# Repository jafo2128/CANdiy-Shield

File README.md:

# CANdiy-Shield
The CANdiy-Shield is a plug-on module for Arduino/Genuino with CAN-Bus (Controller Area Network) connectivity.

## Shop
* [CANdiy-Shield](http://www.watterott.com/en/Arduino-CANdiy-Shield)
* [Railuino Components](http://www.watterott.com/en/Railuino-components)
* [OBD2-Connector](http://www.watterott.com/en/OBD2-Connector-With-PCB)

## Features
* Microchip MCP2515 CAN Controller (SPI)
* Microchip MCP2562 CAN Transceiver (CANdiy-Shield v1.x: MCP2551)
* Switchable between 3V3 or 5V logic level
* 2 CAN connectors (RJ45)
* Prototyping Area
* Compatible with all Arduino/Genuino Boards (SPI connection via 6-Pin ISP connector)

## Hardware and Software
* [Schematics + Layout](https://github.com/watterott/CANdiy-Shield/tree/master/hardware)
* [Arduino Library and Examples](https://github.com/watterott/Arduino-Libs)

## Projects
* Railuino (Maerklin Model Railways): http://code.google.com/p/railuino/
  [German Documentation](https://railuino.googlecode.com/files/2013-08-01-Railuino-Directors-Cut.pdf),
  [German Forum](http://www.stummiforum.de/viewtopic.php?t=90072),
  [German Magazine Article](https://shop.heise.de/katalog/ct-hardware-hacks-1-2013),
  [English Documentation](http://www.yaasan.mints.ne.jp/railuino.html),
  [French Documentation](http://mchobby.be/wiki/index.php?title=Railuino)
* Mechanic (OBD-II Interface): http://code.google.com/p/mechanic/
* Electricity on Tap: http://www.terabatt.com/makerscorner.html
* WikiCAN (OBD On-Board-Diagnostics): http://www.wikican.uni-bayreuth.de/wikican/index.php?title=WikiCAN-Arduino
* MERG CBUS (Model Railways): http://www.oscale.net/cbus http://www.merg.org.uk/merg_resources/cbus.php

Finally words from us Archivers and Developers.. 

##### Donate

People from time to time wish to donate a little money. Donating won't get you anything special, other than a warm feeling inside, and possibly urge me to produce more freely available material for interesting projects. You can donate via [PayPal](https://www.paypal.com), just click [donate](https://www.paypal.com/cgi-bin/webscr?cmd=_s-xclick&hosted_button_id=3PXVSLXFBS45E) button available below - it will redirect you to the secured PayPal page where you can provide donation amount (there is no minimal value). Any donations are apreciated greatly, and we thank you all in advance for your support along the ways..

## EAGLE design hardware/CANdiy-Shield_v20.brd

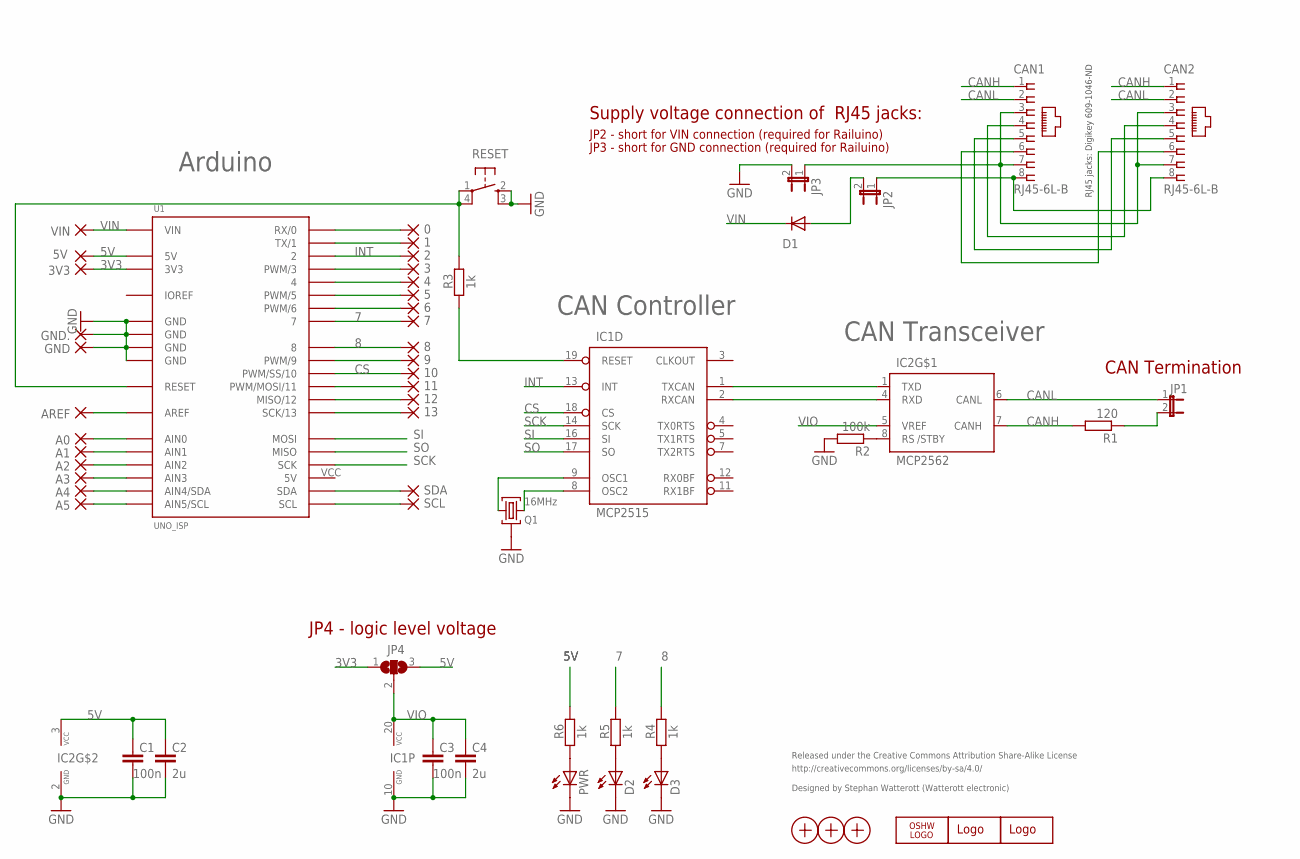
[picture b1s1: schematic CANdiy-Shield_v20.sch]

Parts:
0, 1, 2, 3, 3V3, 4, 5, 5V, 6, 7, 8, 9, 10, 11, 12, 13: 1,6/0,8
A0, A1, A2, A3, A4, A5: 1,6/0,8
AREF: 1,6/0,8
C1, C3: 100n; C0603
C2, C4: 2u; C0603
CAN1, CAN2: RJ45-6L-B; RJ45-NO-SHIELD
D1: CGRM4001-G; SOD-123_MINI-SMA
D2, D3: LEDCHIPLED_0603; CHIPLED_0603
GND, GND.: 1,6/0,8
IC1: MCP2515; TSSOP20
IC2: MCP2562; SO08
JP1, JP2, JP3: JP1E; JP1
JP4: SJ2W; SJ_2
LOGO1: LOGO-SPARK_PLACE; SPARK_TPLACE
LOGO2: OSHW_LOGO_6MILX0100-NT; OSHW_6X100_NOTEXT
PWR: LEDCHIPLED_0603; CHIPLED_0603
Q1: 16MHz; SMD_OSC_35X15
R1: 120; R0603
R2: 100k; R0603
R3, R4, R5, R6: 1k; R0603
RESET: SW_SMDS; SW_SMD4
SCL: 1,6/0,8
SDA: 1,6/0,8
U1: UNO_ISP
U$1: WE-LOGO
VIN: 1,6/0,8
X1, X2, X3: PASSER

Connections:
0: 0.1, U1.0 (RX/0)
1: 1.1, U1.1 (TX/1)
3: 3.1, U1.3 (PWM/3)
3V3: 3V3.1, JP4.1, U1.3V3
4: 4.1, U1.4
5: 5.1, U1.5 (PWM/5)
5V: 5V.1, C1.1, C2.1, IC2.3 (VCC), JP4.3, R6.1, U1.5V
6: 6.1, U1.6 (PWM/6)
7: 7.1, R5.1, U1.7
8: 8.1, R4.1, U1.8
9: 9.1, U1.9 (PWM/9)
11: 11.1, U1.11 (PWM/MOSI/11)
12: 12.1, U1.12 (MISO/12)
13: 13.1, U1.13 (SCK/13)
A0: A0.1, U1.AIN0
A1: A1.1, U1.AIN1
A2: A2.1, U1.AIN2
A3: A3.1, U1.AIN3
A4: A4.1, U1.AIN4 (AIN4/SDA)
A5: A5.1, U1.AIN5 (AIN5/SCL)
AREF: AREF.1, U1.AREF
CANH: CAN1.1, CAN2.1, IC2.7 (CANH), R1.2
CANL: CAN1.2, CAN2.2, IC2.6 (CANL), JP1.1
CAN_RX: IC1.2 (RXCAN), IC2.4 (RXD)
CAN_TX: IC1.1 (TXCAN), IC2.1 (TXD)
CS: 10.1, IC1.18 (CS), U1.10 (PWM/SS/10)
GND: C1.2, C2.2, C3.2, C4.2, D2.C, D3.C, GND.1, GND..1, IC1.10 (GND), IC2.2 (GND), JP3.2, PWR.C, Q1.GND, R2.2, RESET.2 (S), RESET.3 (S1), U1.GND@1 (GND), U1.GND@2 (GND), U1.GND@3 (GND), U1.GND@4 (GND)
INT: 2.1, IC1.13 (INT), U1.2
IOREF: U1.IOREF
unnamed: IC1.19 (RESET), R3.2
unnamed: CAN1.8, CAN2.8, JP2.1
unnamed: IC2.8 (RS), R2.1
unnamed: CAN1.3, CAN1.7, CAN2.3, CAN2.7, JP3.1
unnamed: JP1.2, R1.1
unnamed: SCL.1, U1.SCL
unnamed: SDA.1, U1.SDA
unnamed: D3.A, R4.2
unnamed: PWR.A, R6.2
unnamed: D2.A, R5.2
unnamed: D1.A, JP2.2
unnamed: CAN1.4, CAN2.4
unnamed: CAN1.5, CAN2.5
unnamed: CAN1.6, CAN2.6
OSC1: IC1.9 (OSC1), Q1.1
OSC2: IC1.8 (OSC2), Q1.2
RESET: R3.1, RESET.1, RESET.4 (P1), U1.RST (RESET)
SCK: IC1.14 (SCK), U1.SCK
SI: IC1.16 (SI), U1.MOSI
SO: IC1.17 (SO), U1.MISO
VIN: D1.C, U1.VIN, VIN.1
VIO: C3.1, C4.1, IC1.20 (VCC), IC2.5 (VREF), JP4.2

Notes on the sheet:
Released under the Creative Commons Attribution Share-Alike License
http://creativecommons.org/licenses/by-sa/4.0/
Designed by Stephan Watterott (Watterott electronic)
Arduino
CAN Termination
Supply voltage connection of RJ45 jacks:
JP3 - short for GND connection (required for Railuino)
JP2 - short for VIN connection (required for Railuino)
RJ45 jacks: Digikey 609-1046-ND
CAN Controller
CAN Transceiver
JP4 - logic level voltage
/STBY

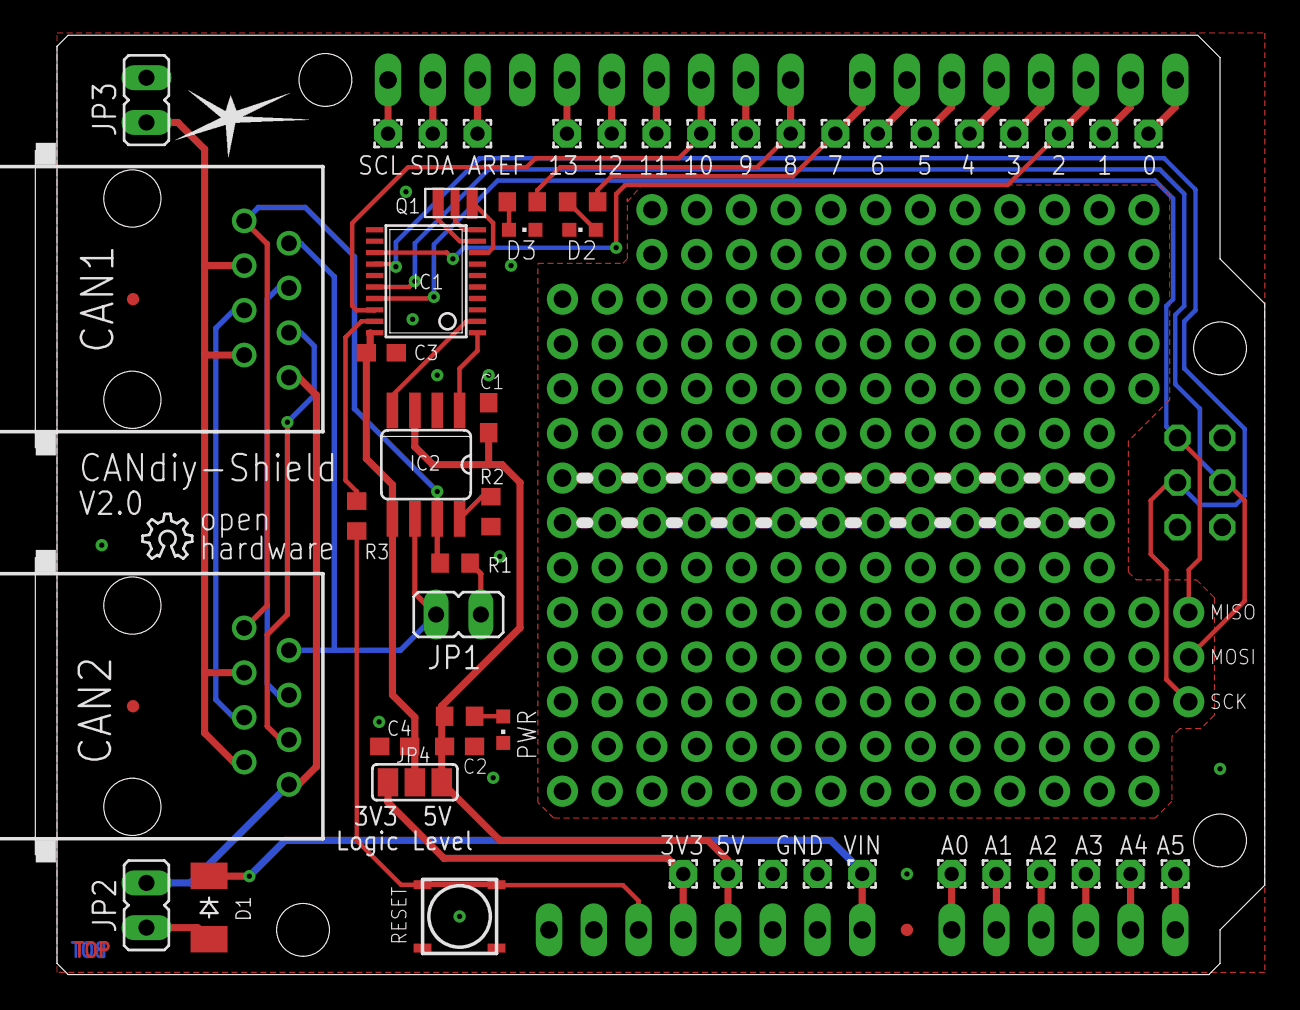
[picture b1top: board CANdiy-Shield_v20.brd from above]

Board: 2 copper layers, 69.8 x 53.3 mm, 59 parts (1 on the bottom side), 50 nets.

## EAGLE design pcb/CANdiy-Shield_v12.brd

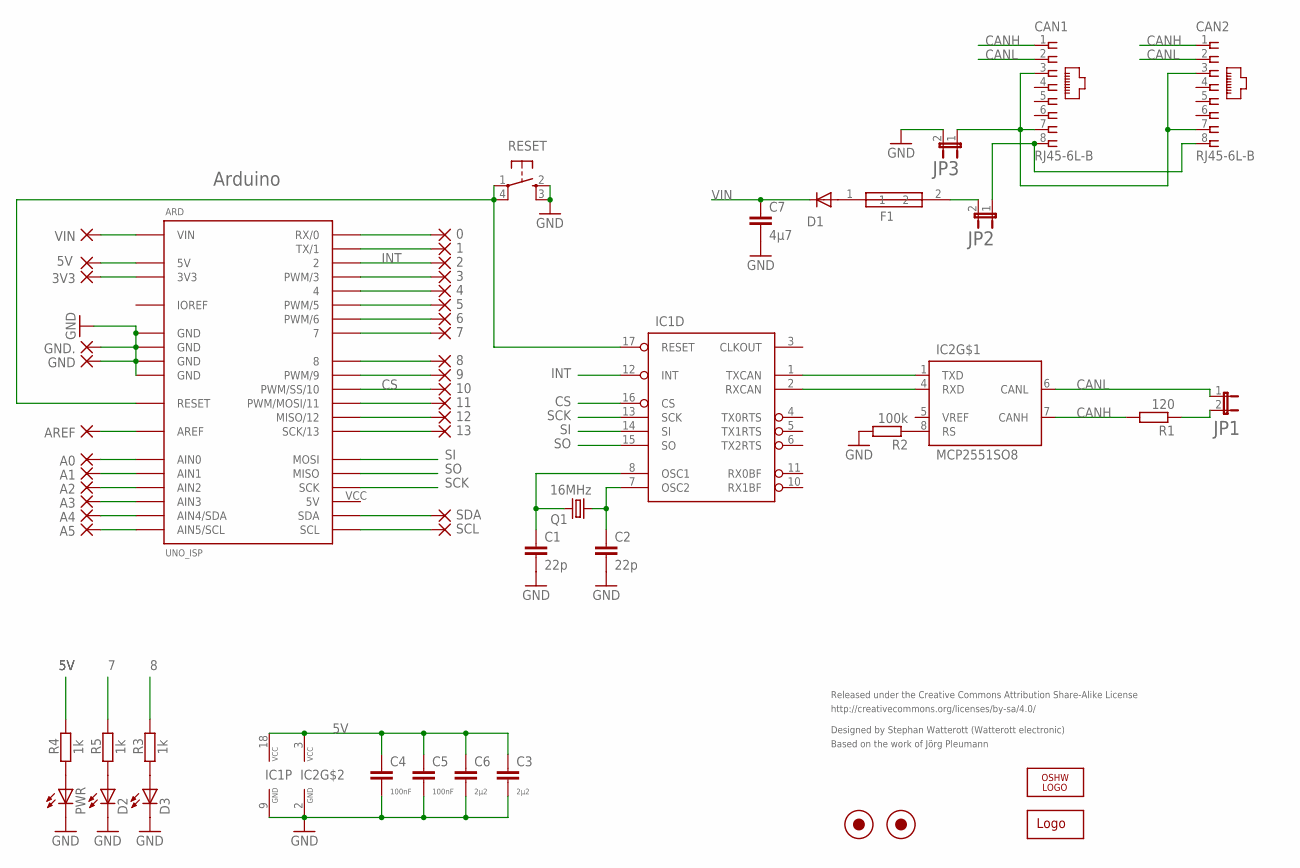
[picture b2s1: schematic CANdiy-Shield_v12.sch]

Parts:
0, 1, 2, 3, 3V3, 4, 5, 5V, 6, 7, 8, 9, 10, 11, 12, 13: 1,6/0,8
A0, A1, A2, A3, A4, A5: 1,6/0,8
ARD: UNO_ISP
AREF: 1,6/0,8
C1, C2: 22p; C0603
C3, C6: 2µ2; C0603
C4, C5: 100nF; C0603
C7: 4µ7; C1206
CAN1, CAN2: RJ45-6L-B; RJ45-NO-SHIELD
D1: CGRM4001-G; SOD-123_MINI-SMA
D2, D3: LEDCHIPLED_0603; CHIPLED_0603
F1: F1; L1812
GND, GND.: 1,6/0,8
IC1: MCP2515SO; SO-18W
IC2: MCP2551SO8; SO08
JP1, JP2, JP3: JP1E; JP1
LOGO2: OSHW_LOGO_6MILX0100-NT; OSHW_6X100_NOTEXT
PWR: LEDCHIPLED_0603; CHIPLED_0603
Q1: 16MHz; HC49UP
R1: 120; R0603
R2: 100k; R0603
R3, R4, R5: 1k; R0603
RESET: SW_SMDS; SW_SMD4
SCL: 1,6/0,8
SDA: 1,6/0,8
U$1: WE-LOGO
VIN: 1,6/0,8
X_1, X_2: PASS_1MM; ROUND_1MM

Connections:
3V3: 3V3.1, ARD.3V3
5V: 5V.1, ARD.5V, C3.1, C4.1, C5.1, C6.1, IC1.18 (VCC), IC2.3 (VCC), R4.1
7: 7.1, ARD.7, R5.1
8: 8.1, ARD.8, R3.1
9: 9.1, ARD.9 (PWM/9)
A0: A0.1, ARD.AIN0
AERF: ARD.AREF, AREF.1
CANH: CAN1.1, CAN2.1, IC2.7 (CANH), R1.2
CANL: CAN1.2, CAN2.2, IC2.6 (CANL), JP1.1
CS: 10.1, ARD.10 (PWM/SS/10), IC1.16 (CS)
GND: ARD.GND@1 (GND), ARD.GND@2 (GND), ARD.GND@3 (GND), ARD.GND@4 (GND), C1.2, C2.2, C3.2, C4.2, C5.2, C6.2, C7.2, D2.C, D3.C, GND.1, GND..1, IC1.9 (GND), IC2.2 (GND), JP3.2, PWR.C, R2.2, RESET.2 (S), RESET.3 (S1)
INT: 2.1, ARD.2, IC1.12 (INT)
IOREF: ARD.IOREF
unnamed: C2.1, IC1.7 (OSC2), Q1.1
unnamed: C1.1, IC1.8 (OSC1), Q1.2
unnamed: CAN1.8, CAN2.8, JP2.1
unnamed: IC2.8 (RS), R2.1
unnamed: CAN1.3, CAN1.7, CAN2.3, CAN2.7, JP3.1
unnamed: JP1.2, R1.1
unnamed: ARD.SCL, SCL.1
unnamed: ARD.SDA, SDA.1
unnamed: D3.A, R3.2
unnamed: PWR.A, R4.2
unnamed: D2.A, R5.2
unnamed: 11.1, ARD.11 (PWM/MOSI/11)
unnamed: 12.1, ARD.12 (MISO/12)
unnamed: 13.1, ARD.13 (SCK/13)
unnamed: 6.1, ARD.6 (PWM/6)
unnamed: 5.1, ARD.5 (PWM/5)
unnamed: 4.1, ARD.4
unnamed: 3.1, ARD.3 (PWM/3)
unnamed: 1.1, ARD.1 (TX/1)
unnamed: 0.1, ARD.0 (RX/0)
unnamed: A1.1, ARD.AIN1
unnamed: A2.1, ARD.AIN2
unnamed: A3.1, ARD.AIN3
unnamed: A4.1, ARD.AIN4 (AIN4/SDA)
unnamed: A5.1, ARD.AIN5 (AIN5/SCL)
unnamed: D1.A, F1.1
unnamed: F1.2, JP2.2
RESET: ARD.RST (RESET), IC1.17 (RESET), RESET.1, RESET.4 (P1)
RXCAN: IC1.2 (RXCAN), IC2.4 (RXD)
SCK: ARD.SCK, IC1.13 (SCK)
SI: ARD.MOSI, IC1.14 (SI)
SO: ARD.MISO, IC1.15 (SO)
TXCAN: IC1.1 (TXCAN), IC2.1 (TXD)
VIN: ARD.VIN, C7.1, D1.C, VIN.1

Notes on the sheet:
Released under the Creative Commons Attribution Share-Alike License
http://creativecommons.org/licenses/by-sa/4.0/
Designed by Stephan Watterott (Watterott electronic)
Arduino
Based on the work of Jörg Pleumann

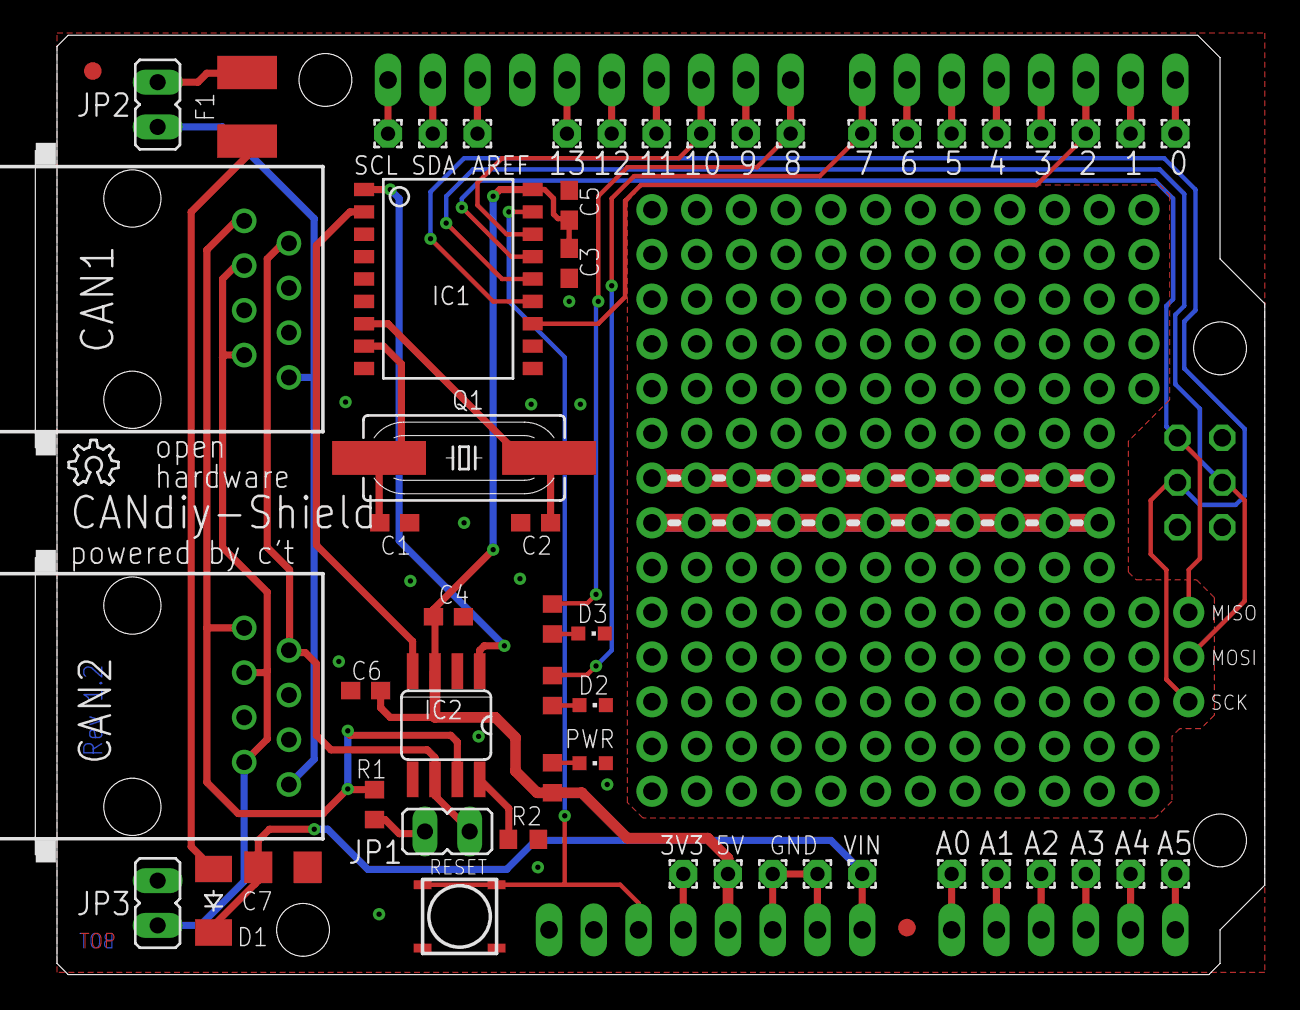
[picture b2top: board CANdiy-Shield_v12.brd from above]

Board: 2 copper layers, 69.8 x 53.3 mm, 59 parts (1 on the bottom side), 46 nets.

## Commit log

2013-02-21 added schematics and layout
2013-03-11 added project list
2013-04-28 added Arduino example and MCP2515 lib
2013-06-10 added jumper infos
2013-06-17 updated projects and readme
2013-08-01 updated pcb
2013-09-26 updated projects
2013-11-18 updated MCP2515 lib
2014-01-02 moved examples to Arduino-Libs repository
2014-04-19 updated schematics and layout files
2014-04-19 updated image
2014-05-13 added infos for connectors
2014-06-11 added v2.0 schematics and layout
2014-08-21 updated layout and schematics
2014-11-06 cleaned up schematics and layout
2015-01-01 updated schematics
2015-01-10 moved image
2015-08-21 changed path structure
